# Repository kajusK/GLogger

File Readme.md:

GLogger
==========

GLogger is minimalistic GPS logger designed with low power consumption in mind.

I was missing a device that would be able to log my hiking and motorbike trips
that were several days long. Using smartphone is no-go for high battery
consumption. Sport watches can work just for two or three days.
Consumer grade GPS loggers sold today are usually designed for sending GPS
location to some cloud.

Features
--------
 * Low battery consumption, can log one location per minute for several weeks,
    designed for more than 40 days of continuous operation
   (turn on at first day of your trip and forget)
 * Measuring distance travelled since power-on and since
   last clear request
 * Powered by CR123 battery or rechargeable equivalent (integrated charger)
 * Lightweight (only TODO grams with battery included)
 * Downloading data from device over USB in GPX format (easy to import to most
   of the sport trackers, etc.), no special PC side software needed

Hardware
========
 * Based on cheap STM32F0 ARM MCU
 * Cheap GPS module SIM28ML, can be replaced with U-Blox (almost pin compatible)
 * External SPI flash for GPS log storage (much lower power consumption than SD
   card)
 * Micro USB for communication with PC
 * OLED display and 2 buttons for user interaction

Software
========
 * Running on top of the [libopencm3](http://libopencm3.org/)
 * Tiny custom graphical library written just for fun
 * Used script from [ChibiOS-Contrib](https://github.com/ChibiOS/ChibiOS-Contrib/blob/master/tools/mx2board.py)
   to generate GPIO configuration from STM32CubeMx without HAL overhead
 * Real time conversion from GPS logs stored in flash to emulated FatFs GPX file

Folders
=======
 * _fw/projects_ - TrueStudio projects for firmware itself, bootloader,...
 * _fw/sources_ - All FW source files
 * _fw/sources/app_ - project specific sources
 * _hw_ - Hardware design files - PCB, enclosure,...
 * _tools_ - various helper scripts
 * _tools/cgui_ - image and font generators for custom GUI

Licensing
=========
The project files can be used under terms in [License_SW](License_SW) and
[License_HW](License_HW).

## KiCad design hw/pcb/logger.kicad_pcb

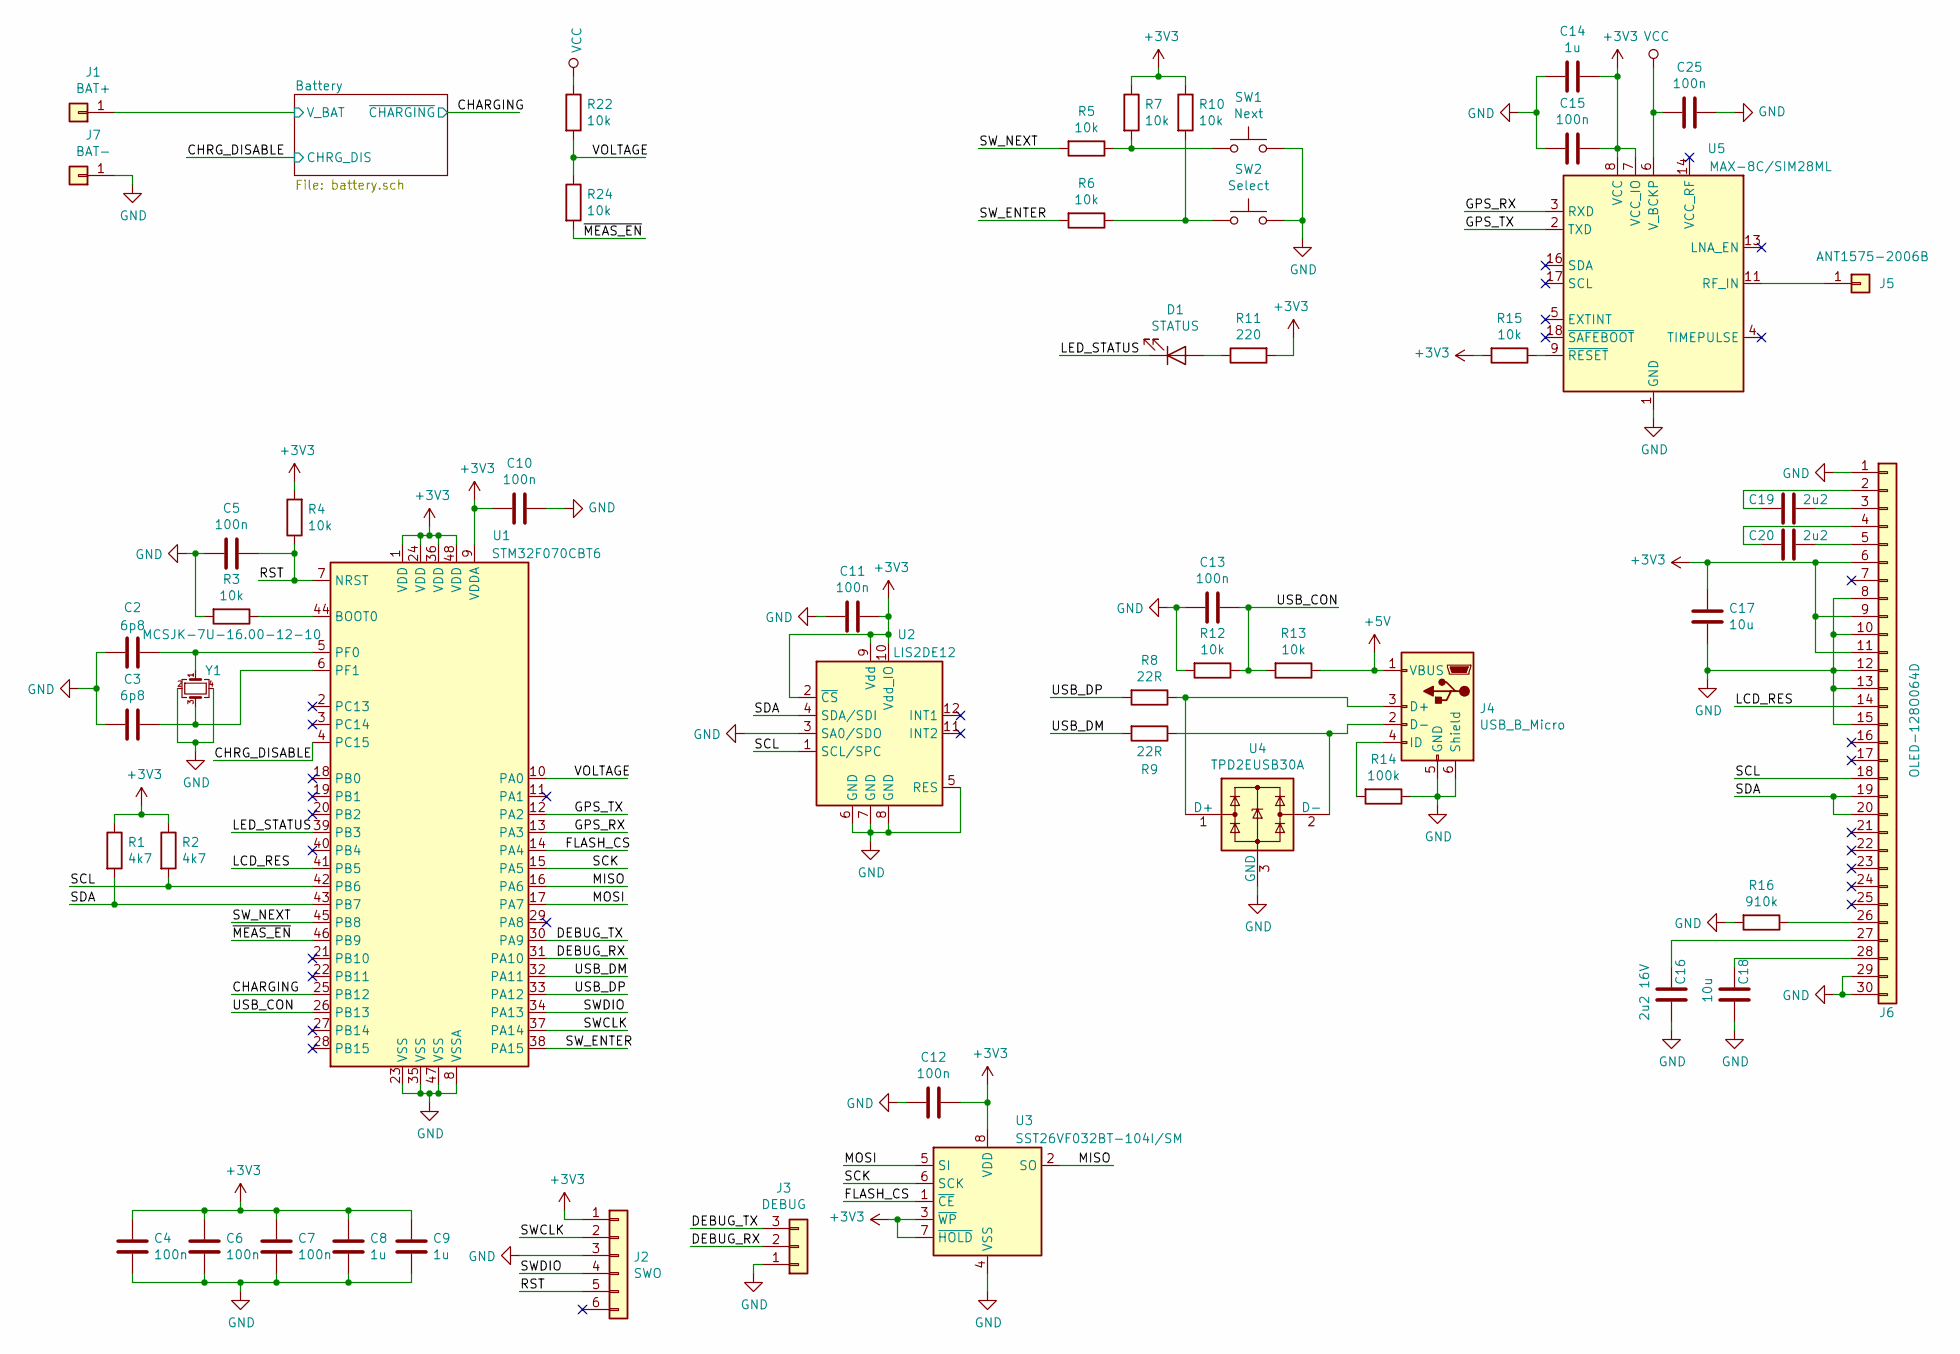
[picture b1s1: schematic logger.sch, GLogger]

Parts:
C2, C3: 6p8; C_0603_1608Metric
C4, C5, C6, C7, C10, C11, C12, C13, C15, C25: 100n; C_0603_1608Metric
C8, C9, C14: 1u; C_0603_1608Metric
C16: 2u2 16V; C_0603_1608Metric
C17, C18: 10u; C_0603_1608Metric
C19, C20: 2u2; C_0603_1608Metric
D1: STATUS; LED_D3.0mm
J1: BAT+; SolderWirePad_1x01_Drill0.8mm
J2: SWO; PinHeader_2x03_P1.27mm_Vertical_SMD
J3: DEBUG; PinSocket_1x03_P1.27mm_Vertical
J4: USB_B_Micro; USB_Micro-B_Amphenol_10103594-0001LF_Horizontal
J5: ANT1575-2006B; SolderWirePad_1x01_Drill1.2mm
J6: OLED-128O064D
J7: BAT-; SolderWirePad_1x01_Drill0.8mm
R1, R2: 4k7; R_0603_1608Metric
R3, R4, R5, R6, R7, R10, R12, R13, R15, R22, R24: 10k; R_0603_1608Metric
R8, R9: 22R; R_0603_1608Metric
R11: 220; R_0603_1608Metric
R14: 100k; R_0603_1608Metric
R16: 910k; R_0603_1608Metric
SW1: Next; SW_SPST_PTS645
SW2: Select; SW_SPST_PTS645
U1: STM32F070CBT6; LQFP-48_7x7mm_P0.5mm
U2: LIS2DE12; LGA-12_2x2mm_P0.5mm
U3: SST26VF032BT-104I/SM; SOIC-8_5.275x5.275mm_P1.27mm
U4: TPD2EUSB30A; Texas_DRT-3
U5: MAX-8C/SIM28ML; ublox_MAX
Y1: MCSJK-7U-16.00-12-10; Crystal_SMD_3225-4Pin_3.2x2.5mm

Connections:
+3V3: C4.1, C6.1, C7.1, C8.1, C9.1, C10.1, C11.1, C12.1, C14.1, C15.1, C17.1, J2.1, J6.6, J6.9, J6.11, R1.1, R2.1, R4.2, R7.1, R10.1, R11.2, R15.2, U1.1 (VDD), U1.9 (VDDA), U1.24 (VDD), U1.36 (VDD), U1.48 (VDD), U2.2 (~CS), U2.9 (Vdd), U2.10 (Vdd_IO), U3.3 (~WP~), U3.7 (~HOLD~), U3.8 (VDD), U5.7 (VCC_IO), U5.8 (VCC); also elsewhere on the board
+5V: J4.1 (VBUS), R13.1; also elsewhere on the board
/Battery/V_BAT: J1.1; also elsewhere on the board
/CHARGING: U1.25 (PB12); also elsewhere on the board
/CHRG_DISABLE: U1.4 (PC15); also elsewhere on the board
/DEBUG_RX: J3.2, U1.31 (PA10)
/DEBUG_TX: J3.3, U1.30 (PA9)
/FLASH_CS: U1.14 (PA4), U3.1 (~CE)
/GPS_RX: U1.13 (PA3), U5.3 (RXD)
/GPS_TX: U1.12 (PA2), U5.2 (TXD)
/LCD_RES: J6.14, U1.41 (PB5)
/LED_STATUS: D1.1 (K), U1.39 (PB3)
/MISO: U1.16 (PA6), U3.2 (SO)
/MOSI: U1.17 (PA7), U3.5 (SI)
/RST: C5.1, J2.5, R4.1, U1.7 (NRST)
/SCK: U1.15 (PA5), U3.6 (SCK)
/SCL: J6.18, R2.2, U1.42 (PB6), U2.1 (SCL/SPC)
/SDA: J6.19, J6.20, R1.2, U1.43 (PB7), U2.4 (SDA/SDI)
/SWCLK: J2.2, U1.37 (PA14)
/SWDIO: J2.4, U1.34 (PA13)
/SW_ENTER: R6.2, U1.38 (PA15)
/SW_NEXT: R5.2, U1.45 (PB8)
/USB_CON: C13.1, R12.1, R13.2, U1.26 (PB13)
/USB_DM: R9.2, U1.32 (PA11)
/USB_DP: R8.2, U1.33 (PA12)
/VOLTAGE: R22.2, R24.1, U1.10 (PA0)
/~MEAS_EN: R24.2, U1.46 (PB9)
GND: C2.2, C3.2, C4.2, C5.2, C6.2, C7.2, C8.2, C9.2, C10.2, C11.2, C12.2, C13.2, C14.2, C15.2, C16.2, C17.2, C18.2, C25.1, J2.3, J3.1, J4.5 (GND), J4.6 (Shield), J6.1, J6.8, J6.10, J6.12, J6.13, J6.15, J6.29, J6.30, J7.1, R3.2, R12.2, R14.1, R16.2, SW1.2, SW2.2, U1.8 (VSSA), U1.23 (VSS), U1.35 (VSS), U1.47 (VSS), U2.3 (SA0/SDO), U2.5 (RES), U2.6 (GND), U2.7 (GND), U2.8 (GND), U3.4 (VSS), U4.3 (GND), U5.1 (GND), U5.10 (GND), U5.12 (GND), Y1.2, Y1.4; also elsewhere on the board
unnamed: C2.1, U1.5 (PF0), Y1.1
unnamed: C3.1, U1.6 (PF1), Y1.3
unnamed: C16.1, J6.27
unnamed: C18.1, J6.28
unnamed: C19.1, J6.3
unnamed: C19.2, J6.2
unnamed: C20.1, J6.5
unnamed: C20.2, J6.4
unnamed: D1.2 (A), R11.1
unnamed: J4.2 (D-), R9.1, U4.2 (D-)
unnamed: J4.3 (D+), R8.1, U4.1 (D+)
unnamed: J4.4 (ID), R14.2
unnamed: J5.1, U5.11 (RF_IN)
unnamed: J6.26, R16.1
unnamed: R3.1, U1.44 (BOOT0)
unnamed: R5.1, R7.2, SW1.1
unnamed: R6.1, R10.2, SW2.1
unnamed: R15.1, U5.9 (~RESET)
VCC: C25.2, R22.1, U5.6 (V_BCKP); also elsewhere on the board

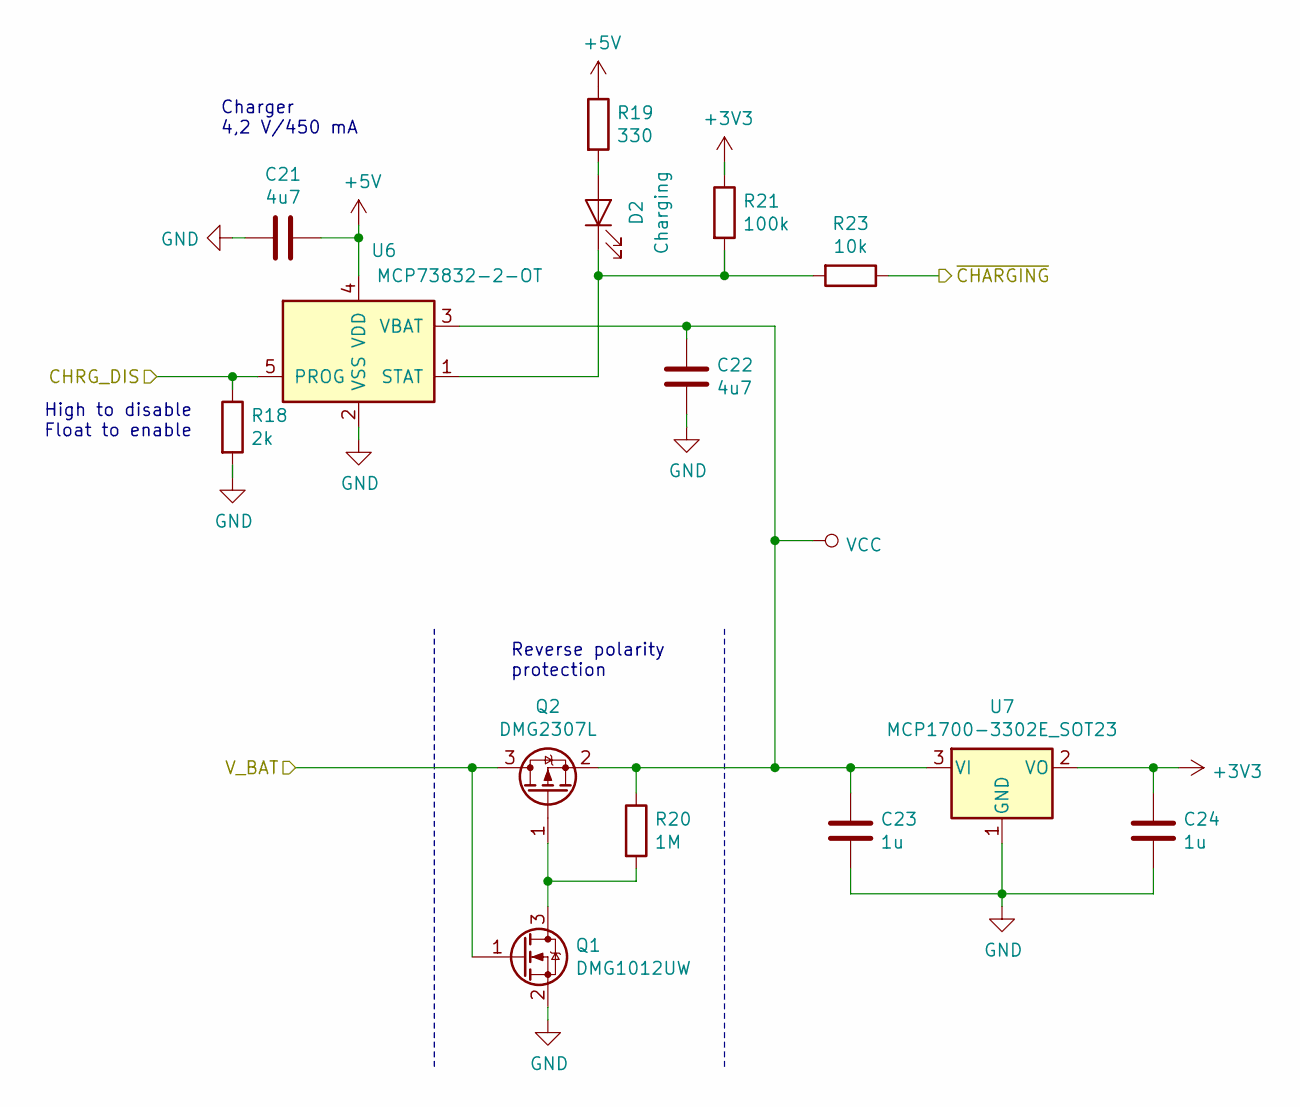
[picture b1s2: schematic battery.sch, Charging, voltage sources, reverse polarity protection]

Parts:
C21, C22: 4u7; C_0603_1608Metric
C23, C24: 1u; C_0603_1608Metric
D2: Charging; LED_D3.0mm
Q1: DMG1012UW; SOT-323_SC-70
Q2: DMG2307L; SOT-23
R18: 2k; R_0603_1608Metric
R19: 330; R_0603_1608Metric
R20: 1M; R_0603_1608Metric
R21: 100k; R_0603_1608Metric
R23: 10k; R_0603_1608Metric
U6: MCP73832-2-OT; SOT-23-5
U7: MCP1700-3302E_SOT23; SOT-23

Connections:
+3V3: C24.1, R21.1, U7.2 (VO); also elsewhere on the board
+5V: C21.1, R19.1, U6.4 (VDD); also elsewhere on the board
/Battery/V_BAT: Q1.1 (G), Q2.3 (D); also elsewhere on the board
/CHARGING: R23.1; also elsewhere on the board
/CHRG_DISABLE: R18.1, U6.5 (PROG); also elsewhere on the board
GND: C21.2, C22.2, C23.2, C24.2, Q1.2 (S), R18.2, U6.2 (VSS), U7.1 (GND); also elsewhere on the board
unnamed: D2.1 (K), R21.2, R23.2, U6.1 (STAT)
unnamed: D2.2 (A), R19.2
unnamed: Q1.3 (D), Q2.1 (G), R20.2
VCC: C22.1, C23.1, Q2.2 (S), R20.1, U6.3 (VBAT), U7.3 (VI); also elsewhere on the board

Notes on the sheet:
High to disable Float to enable
Reverse polarity protection
Charger 4,2 V/450 mA

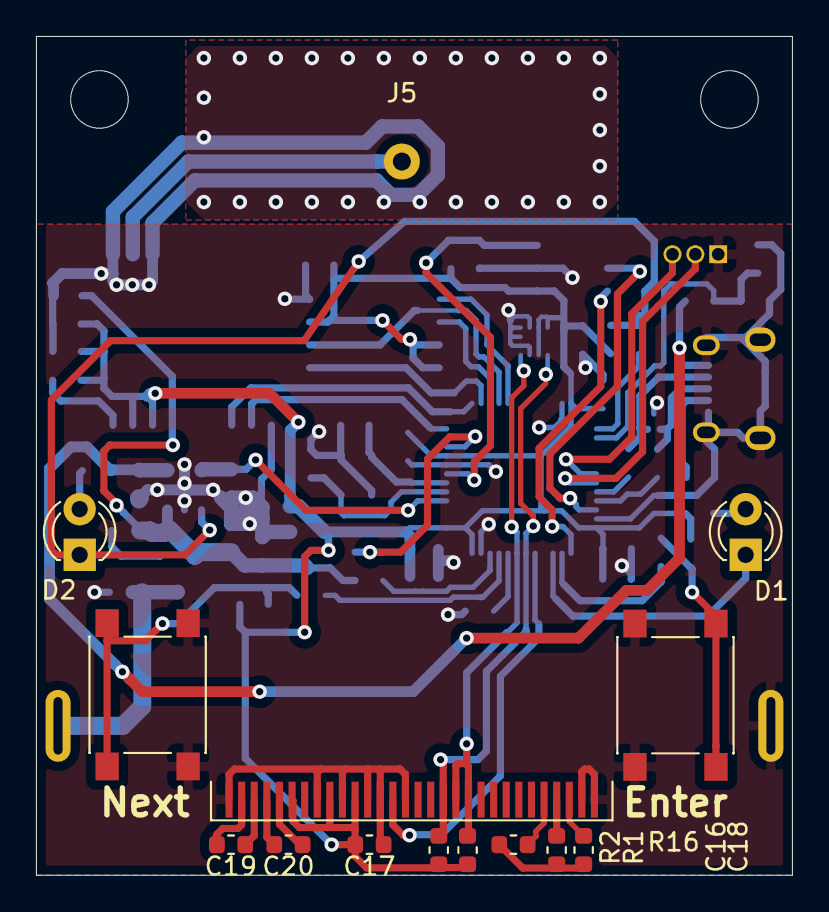
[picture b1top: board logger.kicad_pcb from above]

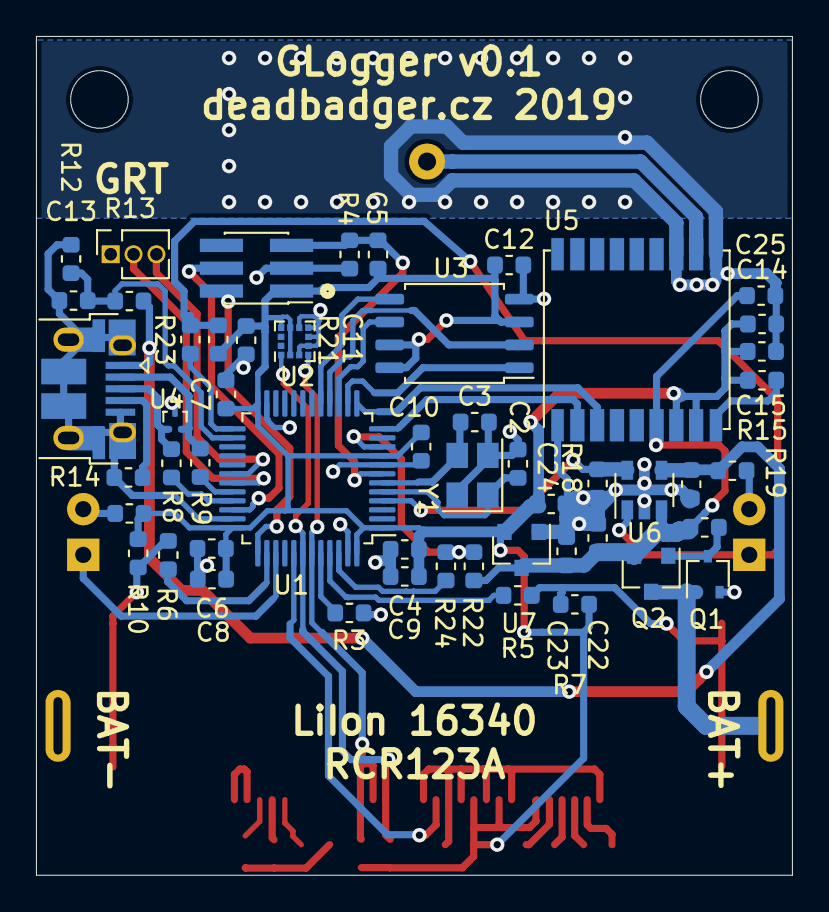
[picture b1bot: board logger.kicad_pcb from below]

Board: 2 copper layers, 42.0 x 46.6 mm, 68 parts (52 on the bottom side), 50 nets.

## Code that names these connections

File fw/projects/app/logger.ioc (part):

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Mcu.Name=STM32F070CBTx
Mcu.Package=LQFP48
Mcu.UserName=STM32F070CBTx
PA0.GPIOParameters=GPIO_Label
PA0.GPIO_Label=VOLTAGE
PA0.Mode=IN0
PA0.Signal=ADC_IN0
PA10.GPIOParameters=GPIO_Label
PA10.GPIO_Label=DEBUG_RX
PA10.Mode=Asynchronous
PA10.Signal=USART1_RX
PA11.Mode=Device
PA11.Signal=USB_DM
PA12.Mode=Device
PA12.Signal=USB_DP
PA13.Mode=Serial_Wire
PA13.Signal=SYS_SWDIO
PA14.Mode=Serial_Wire
PA14.Signal=SYS_SWCLK
PA15.GPIOParameters=GPIO_Label
PA15.GPIO_Label=SW_ENTER
PA15.Signal=GPIO_Input
PA2.GPIOParameters=GPIO_Label
PA2.GPIO_Label=GPS_TX
PA2.Mode=Asynchronous
PA2.Signal=USART2_TX
PA3.GPIOParameters=GPIO_Label
PA3.GPIO_Label=GPS_RX
PA3.Mode=Asynchronous
PA3.Signal=USART2_RX
PA4.GPIOParameters=GPIO_Speed,PinState,GPIO_Label
PA4.GPIO_Label=FLASH_CS
PA4.GPIO_Speed=GPIO_SPEED_FREQ_MEDIUM
PA4.PinState=GPIO_PIN_SET
PA4.Signal=GPIO_Output
PA5.Mode=Full_Duplex_Master
PA5.Signal=SPI1_SCK
PA6.Mode=Full_Duplex_Master
PA6.Signal=SPI1_MISO
PA7.Mode=Full_Duplex_Master
PA7.Signal=SPI1_MOSI
PA9.GPIOParameters=GPIO_Label
PA9.GPIO_Label=DEBUG_TX
PA9.Mode=Asynchronous
PA9.Signal=USART1_TX
PB12.GPIOParameters=GPIO_Label
PB12.GPIO_Label=CHARGING
PB12.Signal=GPIO_Input
PB13.GPIOParameters=GPIO_Label
PB13.GPIO_Label=USB_CON
PB13.Signal=GPIO_Input
PB3.GPIOParameters=GPIO_Label
PB3.GPIO_Label=LED_STATUS
PB3.Signal=GPIO_Output
PB5.GPIOParameters=GPIO_Label
PB5.GPIO_Label=SSD1306_RES
PB5.Signal=GPIO_Output
PB6.Mode=I2C
PB6.Signal=I2C1_SCL
PB7.Mode=I2C
PB7.Signal=I2C1_SDA
PB8.GPIOParameters=GPIO_Label
PB8.GPIO_Label=SW_NEXT
PB8.Signal=GPIO_Input
PB9.GPIOParameters=GPIO_Label
PB9.GPIO_Label=MEAS_EN
PB9.Signal=GPIO_Input
PF0-OSC_IN.Mode=HSE-External-Oscillator
PF0-OSC_IN.Signal=RCC_OSC_IN
PF1-OSC_OUT.Mode=HSE-External-Oscillator
PF1-OSC_OUT.Signal=RCC_OSC_OUT
RCC.HSE_VALUE=16000000
RCC.SYSCLKFreq_VALUE=16000000
RCC.SYSCLKSource=RCC_SYSCLKSOURCE_HSE
board=custom

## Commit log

2019-07-01 Fixed missing include
2019-07-01 Added simple gui library with ssd1306 support
2019-07-01 Added driver for spi flash
2019-07-02 Moved cgui to modules directory
2019-07-02 Added nmea parser
2019-07-02 Added mass storage USB driver
2019-07-02 Added conversion from float to gps coordinates
2019-07-02 Added puts function to uart
2019-07-03 Added ringbuf
2019-07-03 Made scale in nmea float unsigned
2019-07-03 Added GPS driver
2019-07-03 Added missing header
2019-07-03 Added storage for gps records
2019-07-03 Get function for getting amount of items already saved
2019-07-03 Added strograge get size function
2019-07-03 Added trigonometric functions
2019-07-04 Store latitude and longitue in decimal degrees
2019-07-04 Include fonts into main cgui header
2019-07-04 Added route stats calculation
2019-07-07 Fixed usb driver, changed ids and string from hardcoded to defines
2019-07-10 Added integer division with ceil like rounding
2019-07-10 Added FAT16 ramdisk
2019-07-10 Fixed warnings in tests
2019-07-17 Added gpx file generator
2019-07-24 Improved cgui - printf, font metrics,...
2019-08-17 Added firmware update module
2019-08-17 Updated tests gitignore
2019-08-17 Added bootloader draft
2019-08-17 Added support for tab in cgui
2019-08-17 Added gui for logger
2019-08-23 Changed MCU type to one with more pins and flash
2019-09-25 HW revision 0.1
2019-09-30 Updated cube project to match DPS
2019-09-30 Added readme and licenses
2019-09-30 Fixed image path
2019-11-03 Fixed getting spi device
2019-11-03 Added value to crystal caps
2019-11-20 Enable gpio clocks
2019-11-20 Fixed i2c
2019-12-01 Fixed spi flash access
2019-12-01 Fixed i2c clock for fast mode, wait for transmission end before returning after nack
2019-12-02 Fixed typo
2019-12-09 Fixed ssd1306 driver
2019-12-12 Added system logging module
2019-12-12 Added cppcheck to build steps
2019-12-12 Added putc to uart
2019-12-14 Added timeouts to i2c to avoid infinite loop
2019-12-14 Fixed macros in log, set logging uart
2019-12-14 Add altitude to gps output, added debug output for gps messages
2019-12-14 Updated main file to do something
2019-12-15 Fixed building unit tests
2019-12-15 Added button presses processing
2019-12-15 Added getters for screen dimensions to cgui
2019-12-15 Check array bounds when writing to frame buffer
2019-12-15 Initial wroking menu
2020-04-10 Moved common code to external library
2020-04-10 Build with debug symbols
2020-05-18 Added screen with satellite info
2020-05-25 Rewritten menu to store as much as possible in flash
2020-05-25 Moved status screen to menu
2020-10-09 Ported to new format of AFW drivers
2020-10-09 Set Log uart device by function call
2020-10-10 Added a bootloader project, functional fw update over USB
2020-10-11 Updated AFW library
2020-10-11 Updated to latest libopencm3, added linker files
